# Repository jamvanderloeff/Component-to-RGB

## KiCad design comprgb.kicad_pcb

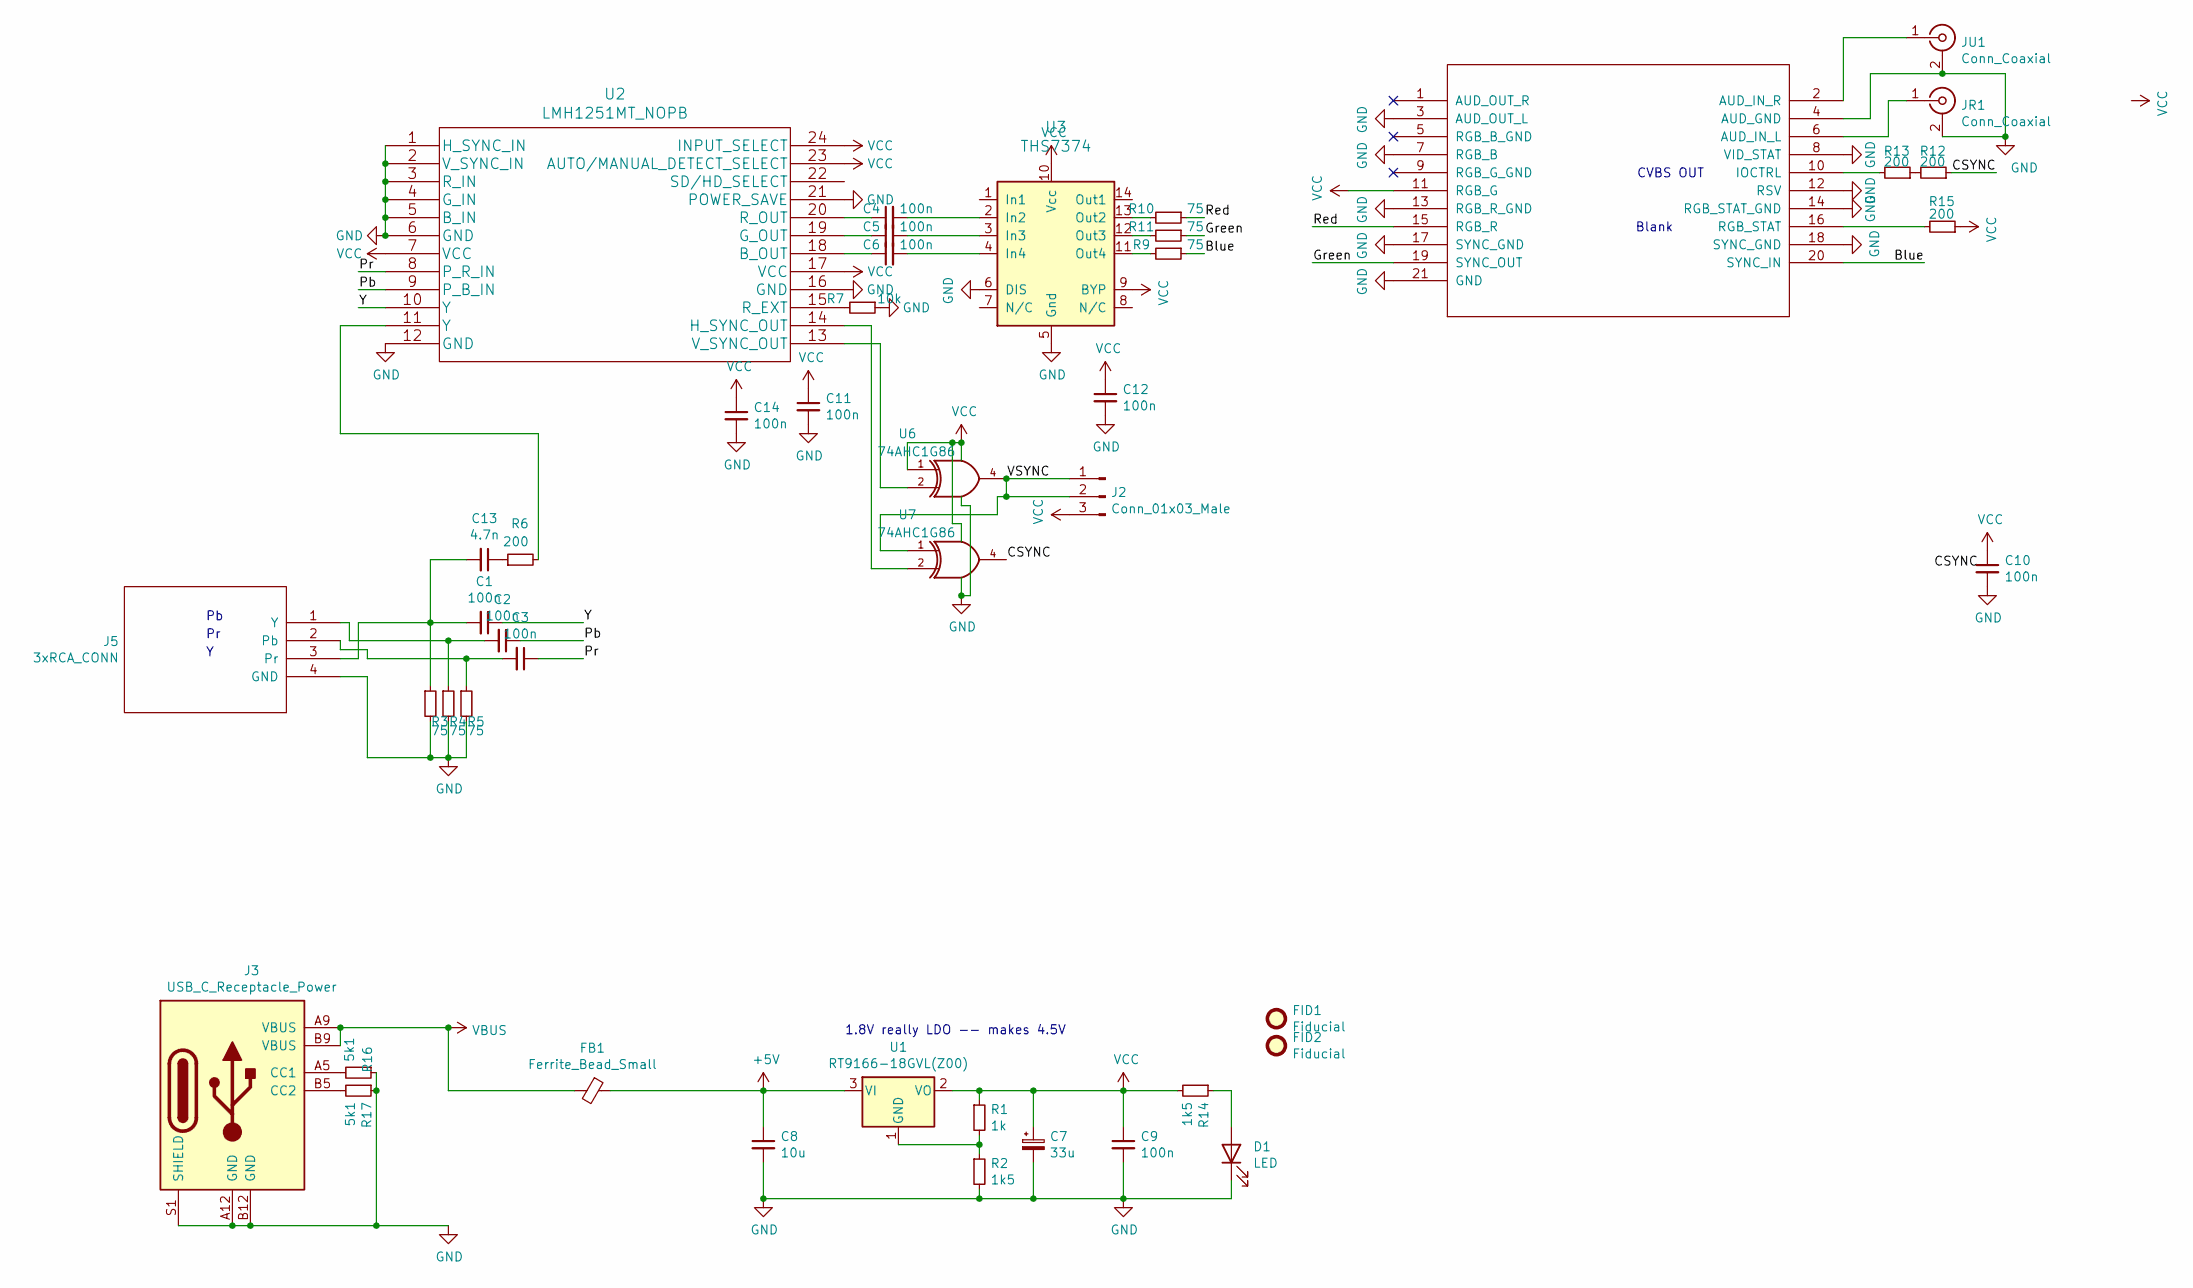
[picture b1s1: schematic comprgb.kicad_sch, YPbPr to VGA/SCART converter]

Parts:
C1, C2, C3, C4, C5, C6, C9, C10, C11, C12, C14: 100n; C_0805_2012Metric; LCSC C28233
C7: 33u; CP_Elec_6.3x7.7; LCSC C47023112
C8: 10u; C_0805_2012Metric; LCSC C45783
C13: 4.7n; C_0805_2012Metric; LCSC C1744
D1: LED; LED_0805_2012Metric; LCSC C84256
FB1: Ferrite_Bead_Small; L_0805_2012Metric; LCSC C1017
FID1: Fiducial; wakaba; LCSC NOT FITTED
FID2: Fiducial; uwusmaller; LCSC NOT FITTED
J2: Conn_01x03_Male; PinHeader_1x03_P2.54mm_Vertical; LCSC NOT FITTED
J3: USB_C_Receptacle_Power; USB_C_Receptacle_Generic_Power_Only; LCSC C283540
J4: SCART_CONN; LCSC NOT FITTED
J5: 3xRCA_CONN; 3xRCA_CONN_SINGLE; LCSC NOT FITTED
JR1: Conn_Coaxial; Cheapo_RCA_single_edge; LCSC NOT FITTED
JU1: Conn_Coaxial; Cheapo_RCA_single_edge; LCSC NOT FITTED
R1: 1k; R_0805_2012Metric; LCSC C17513
R2, R14: 1k5; R_0805_2012Metric; LCSC C4310
R3, R4, R5, R9, R10, R11: 75; R_0805_2012Metric; LCSC C22356789
R6, R12, R13, R15: 200; R_0805_2012Metric; LCSC C17540
R7: 10k; R_0805_2012Metric; LCSC C17414
R16, R17: 5k1; R_0805_2012Metric; LCSC C26023
U1: RT9166-18GVL(Z00); SOT-23; LCSC C2688243
U2: LMH1251MT_NOPB; TSSOP-24_4.4x7.8mm_P0.65mm; LCSC NOT FITTED
U3: THS7374; TSSOP-14_4.4x5mm_P0.65mm; LCSC C2652746
U6, U7: 74AHC1G86; TSOT-23-5; LCSC C7471

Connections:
+5V: C8.1, FB1.1, U1.3 (VI)
/Blue: J4.20 (SYNC_IN), R9.1
/CSYNC: R12.1, U7.4
/Green: J4.19 (SYNC_OUT), R11.1
/Pb: C2.1, U2.9 (P_B_IN)
/Pr: C3.1, U2.8 (P_R_IN)
/Red: J4.15 (RGB_R), R10.1
/VSYNC: J2.1, J2.2, U6.4, U7.1
/Y: C1.1, U2.10 (Y)
GND: C7.2, C8.2, C9.2, C10.2, C11.2, C12.2, C14.2, D1.1 (K), J3.A12 (GND), J3.B12 (GND), J3.S1 (SHIELD), J4.3 (AUD_OUT_L), J4.4 (AUD_GND), J4.7 (RGB_B), J4.8 (VID_STAT), J4.12 (RSV), J4.13 (RGB_R_GND), J4.14 (RGB_STAT_GND), J4.17 (SYNC_GND), J4.18 (SYNC_GND), J4.21 (GND), J5.4 (GND), JR1.2 (Ext), JU1.2 (Ext), R2.2, R3.2, R4.2, R5.2, R7.1, R16.1, R17.1, U2.1 (H_SYNC_IN), U2.2 (V_SYNC_IN), U2.3 (R_IN), U2.4 (G_IN), U2.5 (B_IN), U2.6 (GND), U2.12 (GND), U2.16 (GND), U2.21 (POWER_SAVE), U3.5 (Gnd), U3.6 (DIS), U6.3 (GND), U7.3 (GND)
unnamed: C13.1, R6.1
unnamed: D1.2 (A), R14.1
unnamed: J3.A5 (CC1), R16.2
unnamed: J3.B5 (CC2), R17.2
unnamed: J4.6 (AUD_IN_L), JR1.1 (In)
unnamed: J4.2 (AUD_IN_R), JU1.1 (In)
unnamed: J4.10 (IOCTRL), R13.2
unnamed: J4.16 (RGB_STAT), R15.2
unnamed: C3.2, J5.2 (Pb), R5.1
unnamed: C1.2, C13.2, J5.3 (Pr), R3.1
unnamed: C2.2, J5.1 (Y), R4.1
unnamed: R6.2, U2.11 (Y)
unnamed: R12.2, R13.1
unnamed: R1.2, R2.1, U1.1 (GND)
unnamed: C6.1, U2.18 (B_OUT)
unnamed: C5.1, U2.19 (G_OUT)
unnamed: U2.14 (H_SYNC_OUT), U7.2
unnamed: R7.2, U2.15 (R_EXT)
unnamed: C4.1, U2.20 (R_OUT)
unnamed: U2.13 (V_SYNC_OUT), U6.2
unnamed: C4.2, U3.2 (In2)
unnamed: C5.2, U3.3 (In3)
unnamed: C6.2, U3.4 (In4)
unnamed: R10.2, U3.13 (Out2)
unnamed: R11.2, U3.12 (Out3)
unnamed: R9.2, U3.11 (Out4)
VBUS: FB1.2, J3.A9 (VBUS), J3.B9 (VBUS)
VCC: C7.1, C9.1, C10.1, C11.1, C12.1, C14.1, J2.3, J4.11 (RGB_G), R1.1, R14.2, R15.1, U1.2 (VO), U2.7 (VCC), U2.17 (VCC), U2.23 (AUTO/MANUAL_DETECT_SELECT), U2.24 (INPUT_SELECT), U3.9 (BYP), U3.10 (Vcc), U6.1, U6.5 (VCC), U7.5 (VCC); also elsewhere on the board

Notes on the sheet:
CVBS OUT
1.8V really LDO -- makes 4.5V
Blank

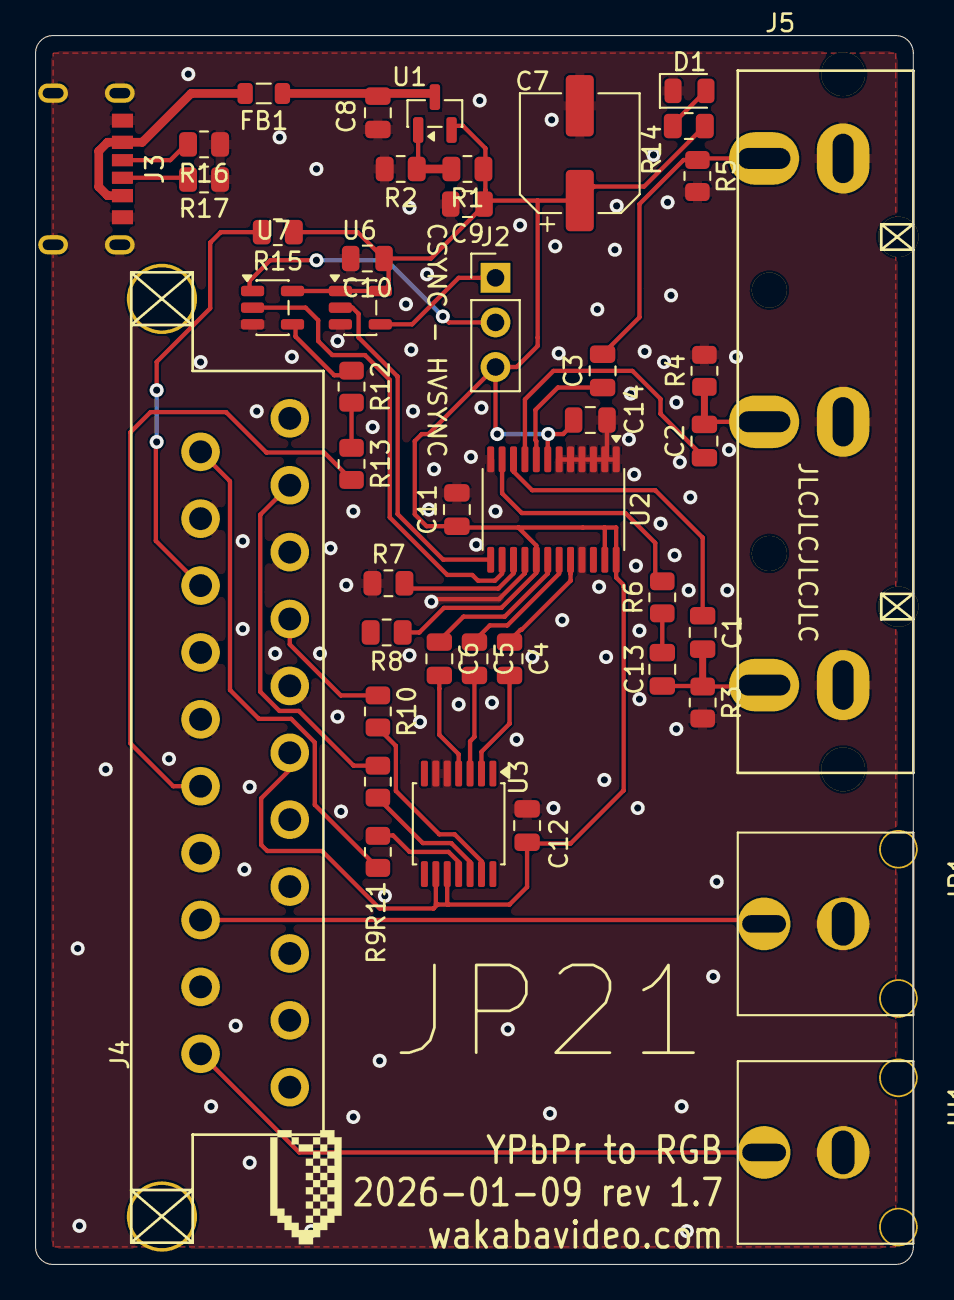
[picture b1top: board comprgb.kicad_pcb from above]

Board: 2 copper layers, 50.0 x 70.0 mm, 45 parts (0 on the bottom side), 38 nets.

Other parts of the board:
R8: 75; R_0805_2012Metric

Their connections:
VCC: R8.1; also elsewhere on the board

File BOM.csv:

Comment,Designator,Footprint,LCSC, LCSC
"100n","C1,C2,C3,C4,C5,C6,C9,C10,C11,C12,C14","Capacitor_SMD:C_0805_2012Metric","","C28323"
"4.7n","C13","Capacitor_SMD:C_0805_2012Metric","","C1744"
"33u","C7","Capacitor_SMD:CP_Elec_6.3x7.7","","C72509"
"10u","C8","Capacitor_SMD:C_0805_2012Metric","","C440198"
"LED","D1","LED_SMD:LED_0805_2012Metric",""
"Ferrite_Bead_Small","FB1","Inductor_SMD:L_0805_2012Metric","","C1017"
"Fiducial","FID1","videobits:wakaba","","NOT FITTED"
"Fiducial","FID2","videobits:uwusmaller","","NOT FITTED"
"VGA","J1","custom_components:VGA_CONN","","NOT FITTED"
"Conn_01x03_Male","J2","Connector_PinHeader_2.54mm:PinHeader_1x03_P2.54mm_Vertical","","NOT FITTED"
"USB_C_Receptacle_Power","J3","videobits:USB_C_Receptacle_Generic_Power_Only","","NOT FITTED"
"SCART_CONN","J4","custom_components:SCART_CONN","","NOT FITTED"
"3xRCA_CONN","J5","videobits:3xRCA_CONN_SINGLE","","NOT FITTED"
"Conn_Coaxial","JR1,JU1","videobits:Cheapo_RCA_single_edge","","NOT FITTED"
"1k","R1","Resistor_SMD:R_0805_2012Metric","","C17513"
"5k1","R17,R16","Resistor_SMD:R_0805_2012Metric","","C27834"
"1k5","R2,R14","Resistor_SMD:R_0805_2012Metric","","C4310"
"75","R3,R4,R5,R11,R10,R9,R8","Resistor_SMD:R_0805_2012Metric","","C20638"
"200","R6,R13,R12","Resistor_SMD:R_0805_2012Metric","","C17540"
"10k","R7","Resistor_SMD:R_0805_2012Metric","","C55866"
"RT9166-18GVL(Z00)","U1","Package_TO_SOT_SMD:SOT-23","","C130827"
"LMH1251MT_NOPB","U2","Package_SO:TSSOP-24_4.4x7.8mm_P0.65mm","","NOT FITTED"
"THS7374","U3","Package_SO:TSSOP-14_4.4x5mm_P0.65mm",""
"74AHC1G86","U6,U7","Package_TO_SOT_SMD:TSOT-23-5","","C7471"

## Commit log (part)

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2021-09-23 bigger gote
2021-11-27 regulator swap, hopefully less shit
2021-11-27 add power led, rebuild gerb
2021-12-09 updated version no
2022-06-29 swap video amp to THS7374 for parts availability
2024-10-15 update to kicad 8, production files
2025-09-12 new prod files
2025-09-12 prod files updated
2025-09-12 updated prod files (totally final this time right)
2025-10-17 corrected r16/17
2025-10-18 updated footprints
2026-01-08 fixed gerbers
2026-01-08 gerbers fixed again
2026-02-01 prod files update
2026-04-24 prod files updated, trace fixed, jlc placeholder
2026-06-10 repo cleanup
2026-06-10 repo cleanup, ignore locks
